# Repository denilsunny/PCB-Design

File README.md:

# PCB-Design
My electronics hardware design and PCB development projects using KiCad.

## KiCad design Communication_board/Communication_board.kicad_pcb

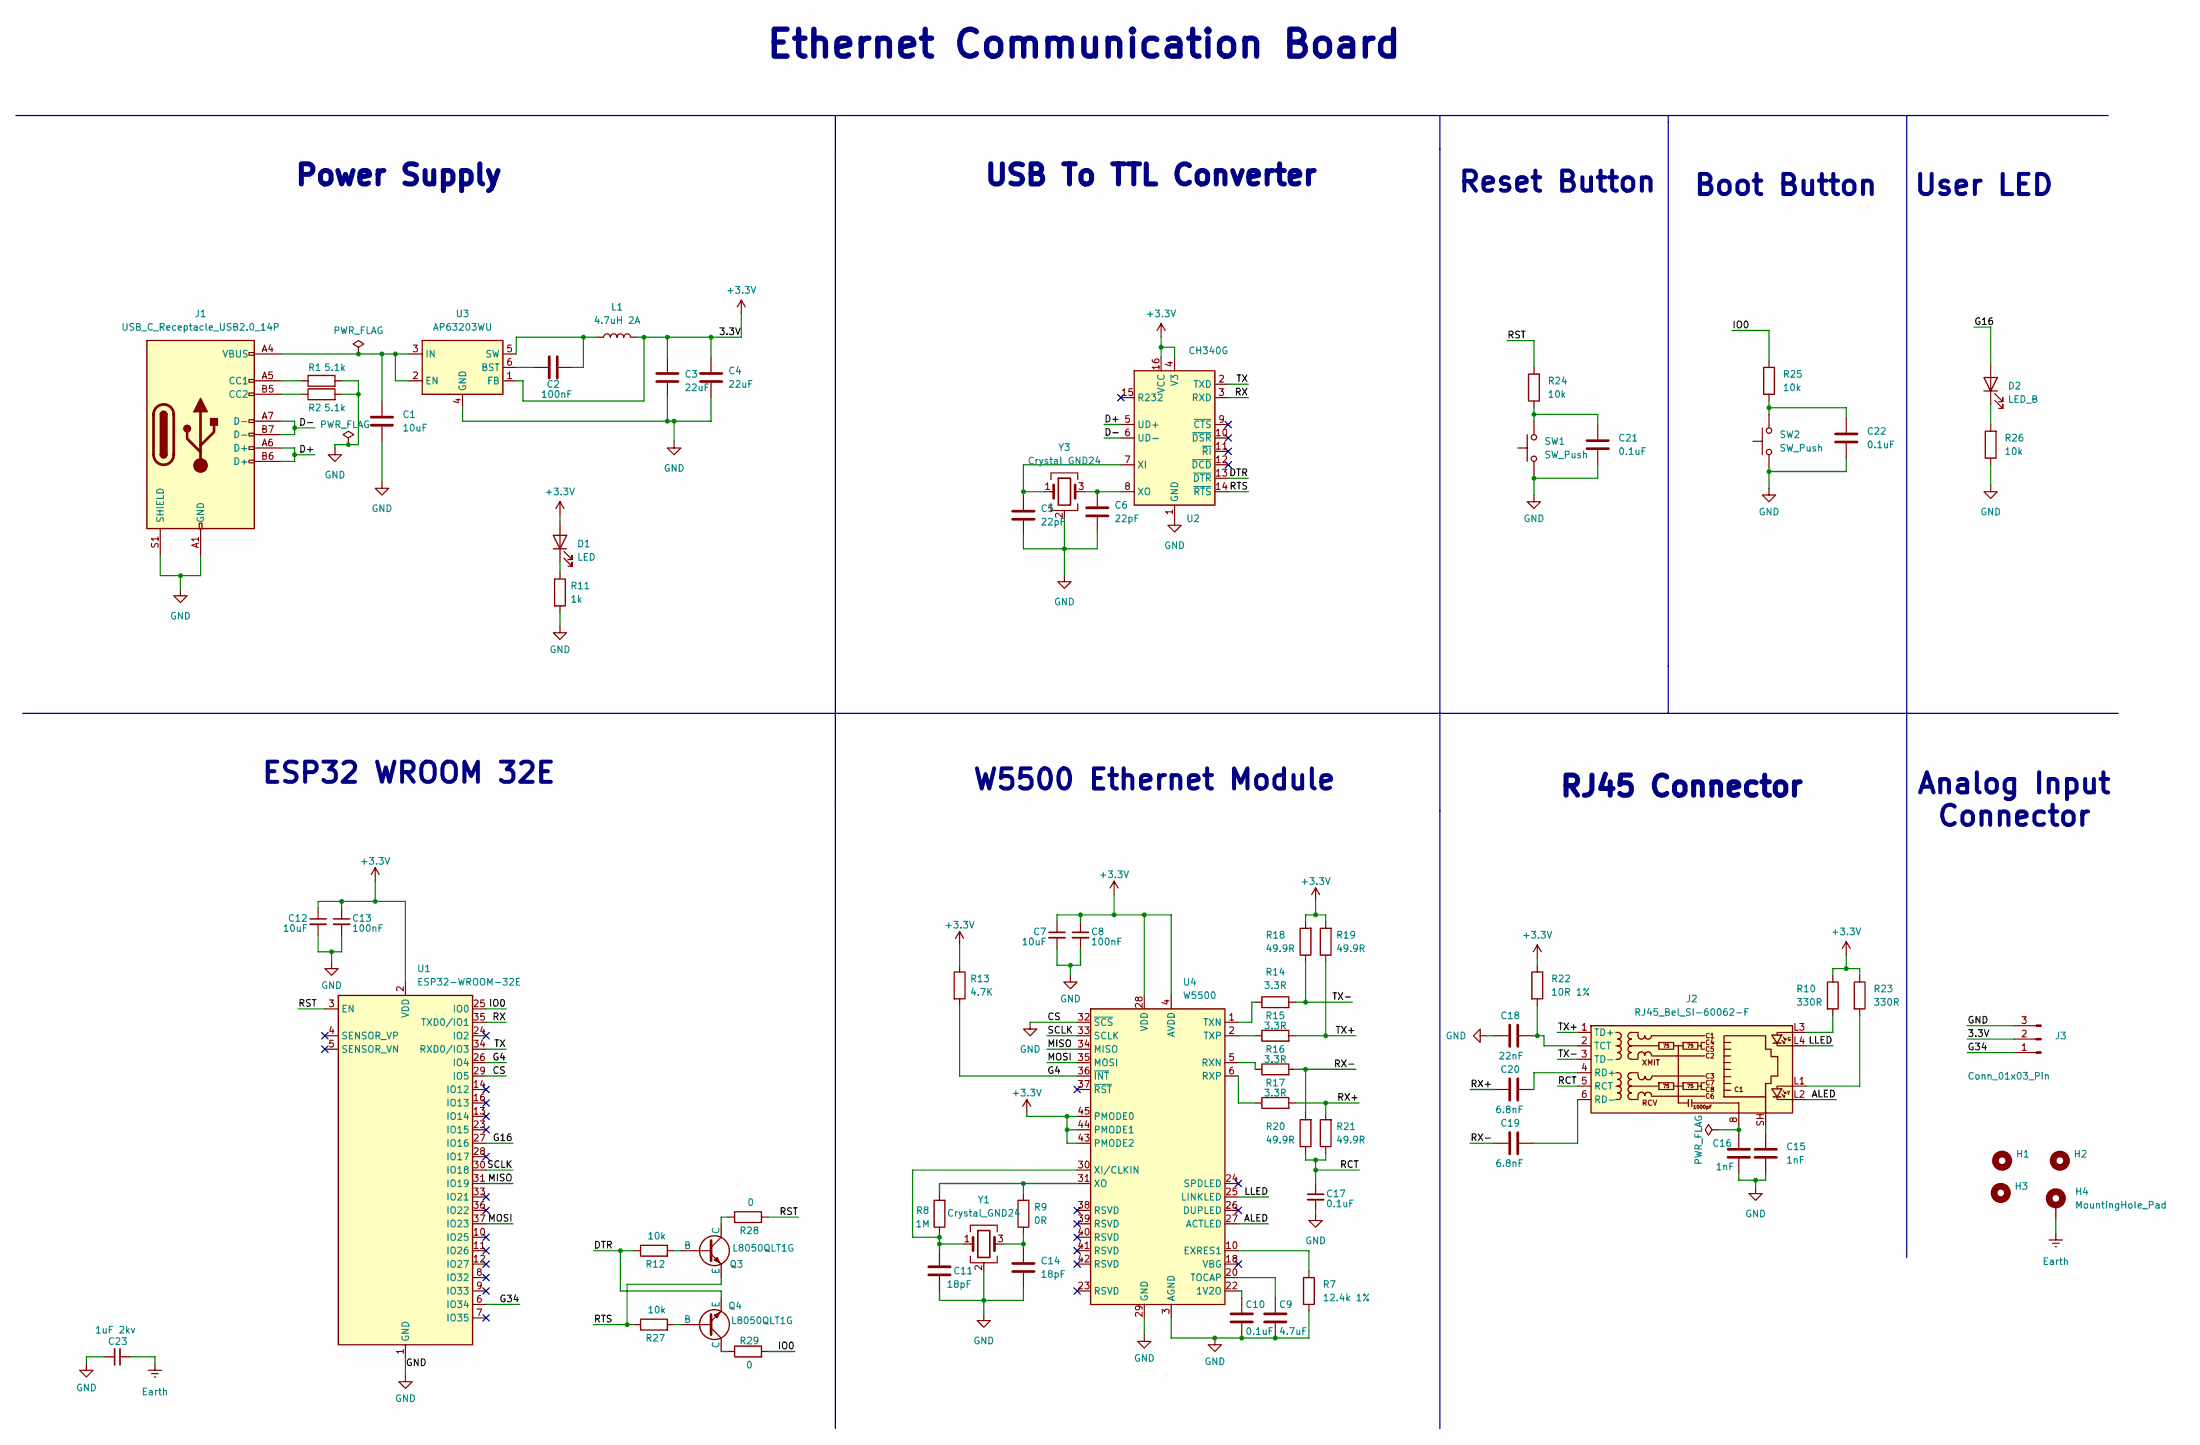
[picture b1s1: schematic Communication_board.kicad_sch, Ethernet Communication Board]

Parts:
C1, C7, C12: 10uF; C_0603_1608Metric
C2, C8, C13: 100nF; C_0603_1608Metric
C3, C4: 22uF; C_0603_1608Metric
C5, C6: 22pF; C_0603_1608Metric
C9: 4.7uF; C_0603_1608Metric
C10, C17, C21, C22: 0.1uF; C_0603_1608Metric
C11, C14: 18pF; C_0603_1608Metric
C15, C16: 1nF; C_0603_1608Metric
C18: 22nF; C_0603_1608Metric
C19, C20: 6.8nF; C_0603_1608Metric
C23: 1uF 2kv; C_0603_1608Metric
D1: LED; LED_0603_1608Metric
D2: LED_B; LED_0603_1608Metric
H1, H2, H3: MountingHole; MountingHole_2.7mm_M2.5
H4: MountingHole_Pad; MountingHole_2.5mm_Pad
J1: USB_C_Receptacle_USB2.0_14P; USB_C_Receptacle_GCT_USB4105-xx-A_16P_TopMnt_Horizontal
J2: RJ45_Bel_SI-60062-F
J3: Conn_01x03_Pin; PinHeader_1x03_P2.54mm_Vertical
L1: 4.7uH 2A; L_Changjiang_FNR252012S
Q3, Q4: L8050QLT1G; SOT-23
R1, R2: 5.1k; R_0603_1608Metric
R7: 12.4k 1%; R_0603_1608Metric
R8: 1M; R_0603_1608Metric
R9: 0R; R_0603_1608Metric
R10, R23: 330R; R_0603_1608Metric
R11: 1k; R_0603_1608Metric
R12, R24, R25, R26, R27: 10k; R_0603_1608Metric
R13: 4.7K; R_0603_1608Metric
R14, R15, R16, R17: 3.3R; R_0603_1608Metric
R18, R19, R20, R21: 49.9R; R_0603_1608Metric
R22: 10R 1%; R_0603_1608Metric
R28, R29: 0; R_0603_1608Metric
SW1, SW2: SW_Push; SW_SPST_PTS810
U1: ESP32-WROOM-32E
U2: CH340G; SOIC-16_3.9x9.9mm_P1.27mm
U3: AP63203WU; TSOT-23-6
U4: W5500; LQFP-48_7x7mm_P0.5mm
Y1, Y3: Crystal_GND24; Crystal_SMD_3225-4Pin_3.2x2.5mm

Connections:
+3.3V: C3.2, C4.2, C7.1, C8.1, C12.1, C13.1, D1.2 (A), J3.2, L1.2, R10.1, R13.1, R18.2, R19.2, R22.1, R23.1, U1.2 (VDD), U2.4 (V3), U2.16 (VCC), U3.1 (FB), U4.4 (AVDD), U4.8 (AVDD), U4.11 (AVDD), U4.15 (AVDD), U4.17 (AVDD), U4.21 (AVDD), U4.28 (VDD), U4.43 (PMODE2), U4.44 (PMODE1), U4.45 (PMODE0)
/ALED: J2.L2, U4.27 (ACTLED)
/D+: J1.A6 (D+), J1.B6 (D+), U2.5 (UD+)
/D-: J1.A7 (D-), J1.B7 (D-), U2.6 (UD-)
/DTR: Q4.3 (E), R12.1, U2.13 (~DTR)
/G4: R13.2, U1.26 (IO4), U4.36 (~INT)
/G16: D2.2 (A), U1.27 (IO16)
/G34: J3.1, U1.6 (IO34)
/IO0: R25.2, R29.2, U1.25 (IO0)
/LLED: J2.L4, U4.25 (LINKLED)
/MISO: U1.31 (IO19), U4.34 (MISO)
/MOSI: U1.37 (IO23), U4.35 (MOSI)
/RCT: C17.1, J2.5 (RCT), R20.1, R21.1
/RST: R24.2, R28.2, U1.3 (EN)
/RTS: Q3.3 (E), R27.1, U2.14 (~RTS)
/RX: U1.35 (TXD0/IO1), U2.3 (RXD)
/RX+: C20.1, R17.2, R21.2
/RX-: C19.1, R16.2, R20.2
/SCLK: U1.30 (IO18), U4.33 (SCLK)
/TX: U1.34 (RXD0/IO3), U2.2 (TXD)
/TX+: J2.1 (TD+), R15.2, R19.1
/TX-: J2.3 (TD-), R14.2, R18.1
Earth: C23.2, H4.1
GND: C1.2, C3.1, C4.1, C5.2, C6.2, C7.2, C8.2, C9.2, C10.2, C11.2, C12.2, C13.2, C14.2, C15.2, C16.2, C17.2, C18.1, C21.2, C22.2, C23.1, J1.A1 (GND), J1.A12 (GND), J1.B1 (GND), J1.B12 (GND), J1.S1 (SHIELD), J3.3, R1.2, R2.2, R7.2, R11.2, R26.1, SW1.1, SW2.1, U1.1 (GND), U1.15 (GND), U1.29 (IO5), U1.38 (GND), U1.39 (GND), U2.1 (GND), U3.4 (GND), U4.3 (AGND), U4.9 (AGND), U4.14 (AGND), U4.16 (AGND), U4.19 (AGND), U4.29 (GND), U4.32 (~SCS), U4.48 (AGND), Y1.2 (G), Y1.4 (G), Y3.2 (G), Y3.4 (G)
unnamed: C14.1, R9.1, Y1.3
unnamed: C15.1, J2.SH
unnamed: C16.1, J2.8
unnamed: C21.1, R24.1, SW1.2
unnamed: C22.1, R25.1, SW2.2
unnamed: D1.1 (K), R11.1
unnamed: D2.1 (K), R26.2
unnamed: J1.A5 (CC1), R1.1
unnamed: J1.B5 (CC2), R2.1
unnamed: J2.L1, R23.2
unnamed: J2.L3, R10.2
unnamed: C20.2, J2.4 (RD+)
unnamed: C19.2, J2.6 (RD-)
unnamed: C18.2, J2.2 (TCT), R22.2
unnamed: Q3.2 (B), R12.2
unnamed: Q3.1 (C), R28.1
unnamed: Q4.2 (B), R27.2
unnamed: Q4.1 (C), R29.1
unnamed: C5.1, U2.7 (XI), Y3.1
unnamed: C6.1, U2.8 (XO), Y3.3
unnamed: C2.1, U3.6 (BST)
unnamed: C1.1, J1.A4 (VBUS), J1.A9 (VBUS), J1.B4 (VBUS), J1.B9 (VBUS), U3.2 (EN), U3.3 (IN)
unnamed: C2.2, L1.1, U3.5 (SW)
unnamed: C10.1, U4.22 (1V2O)
unnamed: R7.1, U4.10 (EXRES1)
unnamed: R16.1, U4.5 (RXN)
unnamed: R17.1, U4.6 (RXP)
unnamed: C9.1, U4.20 (TOCAP)
unnamed: R14.1, U4.1 (TXN)
unnamed: R15.1, U4.2 (TXP)
unnamed: C11.1, R8.1, U4.30 (XI/CLKIN), Y1.1
unnamed: R8.2, R9.2, U4.31 (XO)

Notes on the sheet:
ESP32 WROOM 32E
Power Supply
Boot Button
Analog Input Connector
USB To TTL Converter
Reset Button
Ethernet Communication Board
User LED
W5500 Ethernet Module
RJ45 Connector

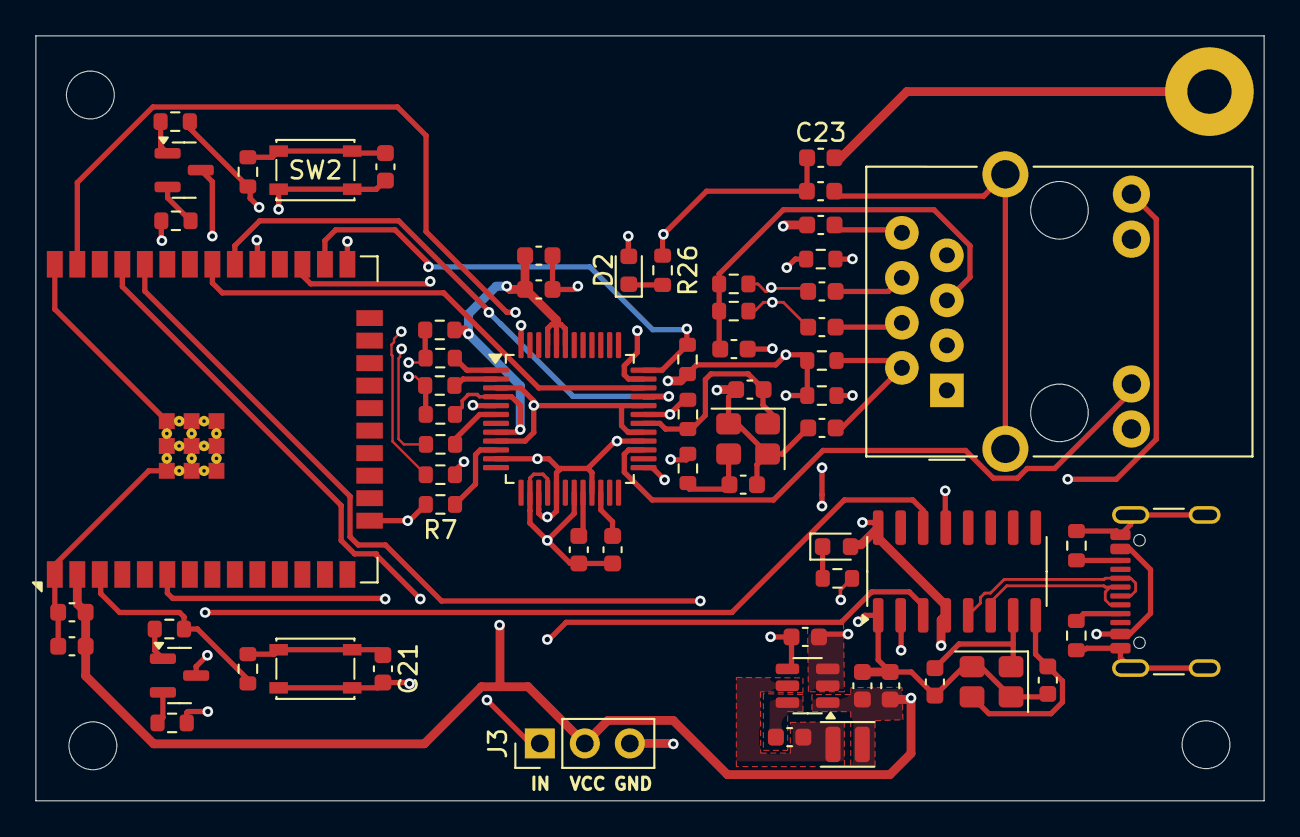
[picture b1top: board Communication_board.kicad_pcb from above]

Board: 4 copper layers, 69.3 x 43.2 mm, 68 parts (0 on the bottom side), 56 nets.

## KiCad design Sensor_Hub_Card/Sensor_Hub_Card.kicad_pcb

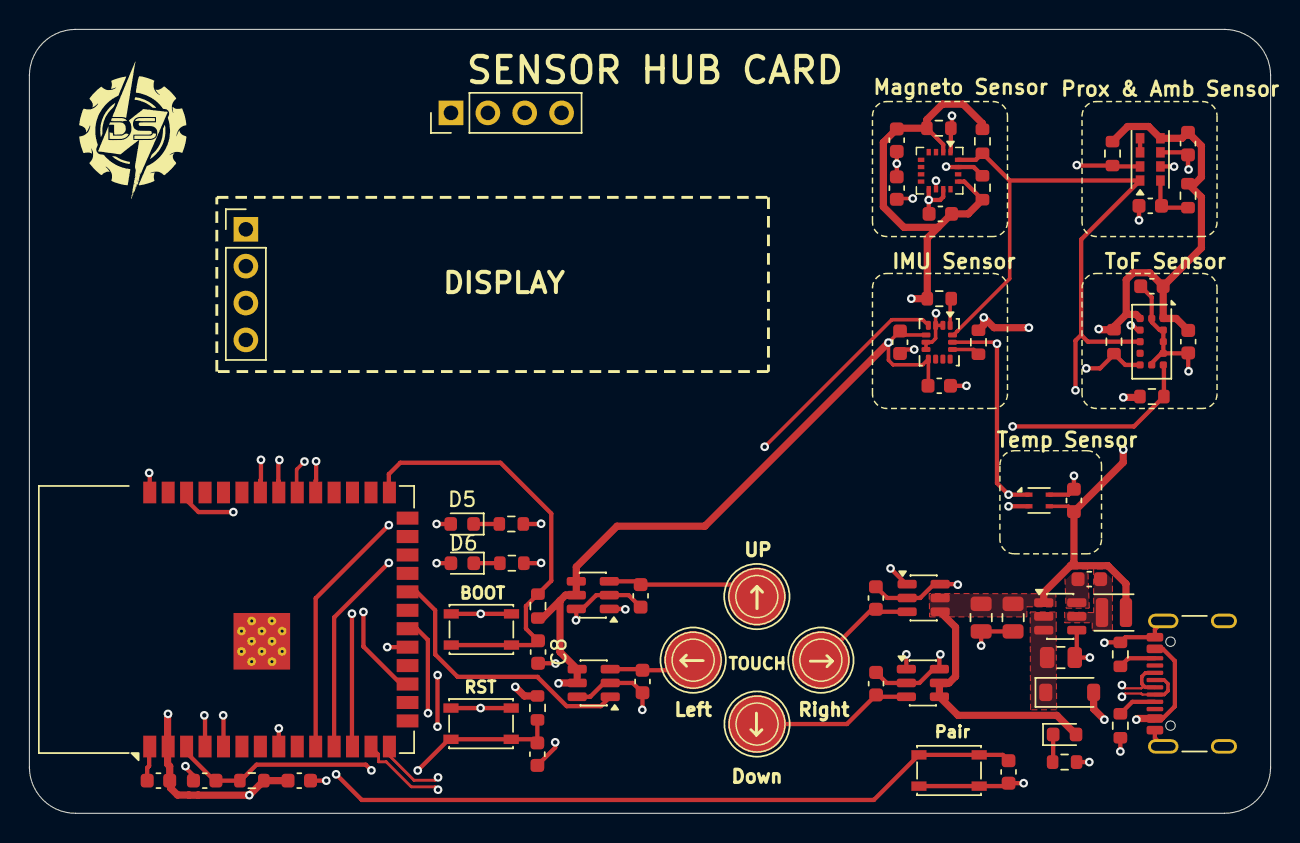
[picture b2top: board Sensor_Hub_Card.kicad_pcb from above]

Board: 4 copper layers, 85.5 x 54.0 mm, 67 parts (0 on the bottom side), 40 nets.

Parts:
C1, C17: 10uF; C_0603_1608Metric
C2, C4, C9, C10, C11, C14: 100nF; C_0603_1608Metric
C3: 10uF; C_0805_2012Metric
C5, C7: 22uF; C_0805_2012Metric
C8, C20: 0.1uF; C_0603_1608Metric
C12, C13, C16, C18, C19, C22: 1uF; C_0603_1608Metric
C15: 4.7nF; C_0603_1608Metric
C23, C26, C27, C28: 30pF; C_0603_1608Metric
D1: B5819W; D_SOD-123
D2, D5, D6: LED_R; LED_0603_1608Metric
Down: Touch; TestPoint_Pad_D4.0mm
J1: USB4500-03-0-A; USB_C_Receptacle_GCT_USB4105-xx-A_16P_TopMnt_Horizontal
J2, J2#2: Conn_01x04; PinHeader_1x04_P2.54mm_Vertical
L1: 4.7uH 2A; L_Changjiang_FNR252012S
Left: Touch; TestPoint_Pad_D4.0mm
R1, R16: 10K; R_0603_1608Metric
R2, R3: 5.1k; R_0603_1608Metric
R4, R5, R6: 1K; R_0603_1608Metric
R7, R8, R9, R11, R12, R13, R14, R15, R17: 10k; R_0603_1608Metric
R10: 22; R_0603_1608Metric
Right: Touch; TestPoint_Pad_D4.0mm
SW2, SW2#2, SW4: SW_Push; SW_SPST_PTS810
TP6: Touch; TestPoint_Pad_D4.0mm
U1: ESP32-S3-WROOM-1
U2: AP63203WU; TSOT-23-6
U3: SHT4x; Sensirion_DFN-4_1.5x1.5mm_P0.8mm_SHT4x_NoCentralPad
U4: LSM6DS3; LGA-14_3x2.5mm_P0.5mm_LayoutBorder3x4y
U5: APDS-9960; Avago_APDS-9960
U6: VL53L1CXV0FY1; ST_VL53L1x
U7: MMC5883MA; LGA-16_3x3mm_P0.5mm
U10, U13, U14, U15: TTP223-BA6; SOT-23-6

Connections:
+3.3V: C1.1, C2.1, C5.1, C7.1, C9.1, C10.1, C11.1, C13.2, C14.1, C15.1, C16.2, C18.2, D2.2 (A), J2.1, J2#2.1, L1.2, R1.1, R7.2, R8.2, R9.2, R10.2, R11.2, R12.2, R13.2, R14.2, R15.2, R16.1, R17.1, U1.2 (3V3), U2.1 (FB), U3.3 (VDD), U4.5 (VDDIO), U4.8 (VDD), U5.5 (LED_A), U6.1 (AVDDVCSEL), U6.11 (AVDD), U7.2 (VDD), U7.13 (VDDIO), U10.4 (AHLB), U10.5 (VDD), U13.4 (AHLB), U13.5 (VDD), U14.4 (AHLB), U14.5 (VDD), U15.4 (AHLB), U15.5 (VDD)
/Boot: C8.1, R17.2, SW2.2, U1.27 (IO0)
/D+: J1.A6 (D+), J1.B6 (D+), U1.14 (USB_D+)
/D-: J1.A7 (D-), J1.B7 (D-), U1.13 (USB_D-)
/GPIO1: R13.1, U1.31 (IO38), U6.7 (GPIO1)
/INT1: U1.32 (IO39), U4.4 (INT1)
/INTAD: R9.1, U1.33 (IO40), U5.2 (INT)
/INTMG: R15.1, U1.34 (IO41), U7.15 (INT)
/LED1: D5.2 (A), U1.10 (IO17)
/LED2: D6.2 (A), U1.11 (IO18)
/Pair: C22.1, SW4.2, U1.8 (IO15)
/RST: C19.1, C20.1, R1.2, R16.2, SW2#2.2, U1.3 (EN)
/SCL: R14.1, U1.17 (IO9), U3.1 (SDA), U4.13 (SCL), U5.7 (SCL), U6.10 (SCL), U7.1 (SCL)
/SCL1: J2.4, J2#2.4, U1.5 (IO5)
/SDA: R11.1, U1.12 (IO8), U3.2 (SCL), U4.14 (SDA), U5.1 (SDA), U6.9 (SDA), U7.16 (SDA)
/SDA1: J2.3, J2#2.3, U1.4 (IO4)
/T1: U1.19 (IO11), U10.1 (Q)
/T2: U1.20 (IO12), U14.1 (Q)
/T3: U1.21 (IO13), U13.1 (Q)
/T4: U1.22 (IO14), U15.1 (Q)
/XSHUNT: R12.1, U1.38 (IO2), U6.5 (XSHUT)
GND: C1.2, C2.2, C3.2, C5.2, C7.2, C8.2, C9.2, C10.2, C11.2, C12.2, C13.1, C14.2, C15.2, C16.1, C17.1, C18.1, C19.2, C20.2, C22.2, C23.2, C26.2, C27.2, C28.2, J1.A1 (GND), J1.A12 (GND), J1.B1 (GND), J1.B12 (GND), J1.S1 (SHIELD), J2.2, J2#2.2, R2.2, R3.2, R4.2, R5.2, R6.2, SW2.1, SW2#2.1, SW4.1, U1.1 (GND), U1.40 (GND), U1.41 (GND), U2.4 (GND), U3.4 (VSS), U4.2 (SDX), U4.3 (SCX), U4.6 (GND), U4.7 (GND), U5.6 (GND), U6.2 (AVSSVCSEL), U6.3 (GND), U6.4 (GND), U6.6 (GND), U6.12 (GND), U7.9 (GND), U7.11 (GND), U10.2 (VSS), U10.6 (TOG), U13.2 (VSS), U13.6 (TOG), U14.2 (VSS), U14.6 (TOG), U15.2 (VSS), U15.6 (TOG)
unnamed: C3.1, D1.1 (K), U2.2 (EN), U2.3 (IN)
unnamed: D2.1 (K), R5.1
unnamed: D5.1 (K), R4.1
unnamed: D6.1 (K), R6.1
unnamed: J1.A5 (CC1), R2.1
unnamed: J1.B5 (CC2), R3.1
unnamed: C4.2, U2.6 (BST)
unnamed: C4.1, L1.1, U2.5 (SW)
unnamed: R7.1, U4.12 (CS)
unnamed: R8.1, U4.1 (SDO/SA0)
unnamed: U5.3 (LDR), U5.4 (LED_K)
unnamed: C12.1, R10.1, U5.8 (VDD)
unnamed: C17.2, U7.10 (CAP)
unnamed: C23.1, Right.1, U10.3 (I)
unnamed: C26.1, TP6.1, U13.3 (I)
unnamed: C27.1, Down.1, U14.3 (I)
unnamed: C28.1, Left.1, U15.3 (I)
VBUS: D1.2 (A), J1.A4 (VBUS), J1.A9 (VBUS), J1.B4 (VBUS), J1.B9 (VBUS)

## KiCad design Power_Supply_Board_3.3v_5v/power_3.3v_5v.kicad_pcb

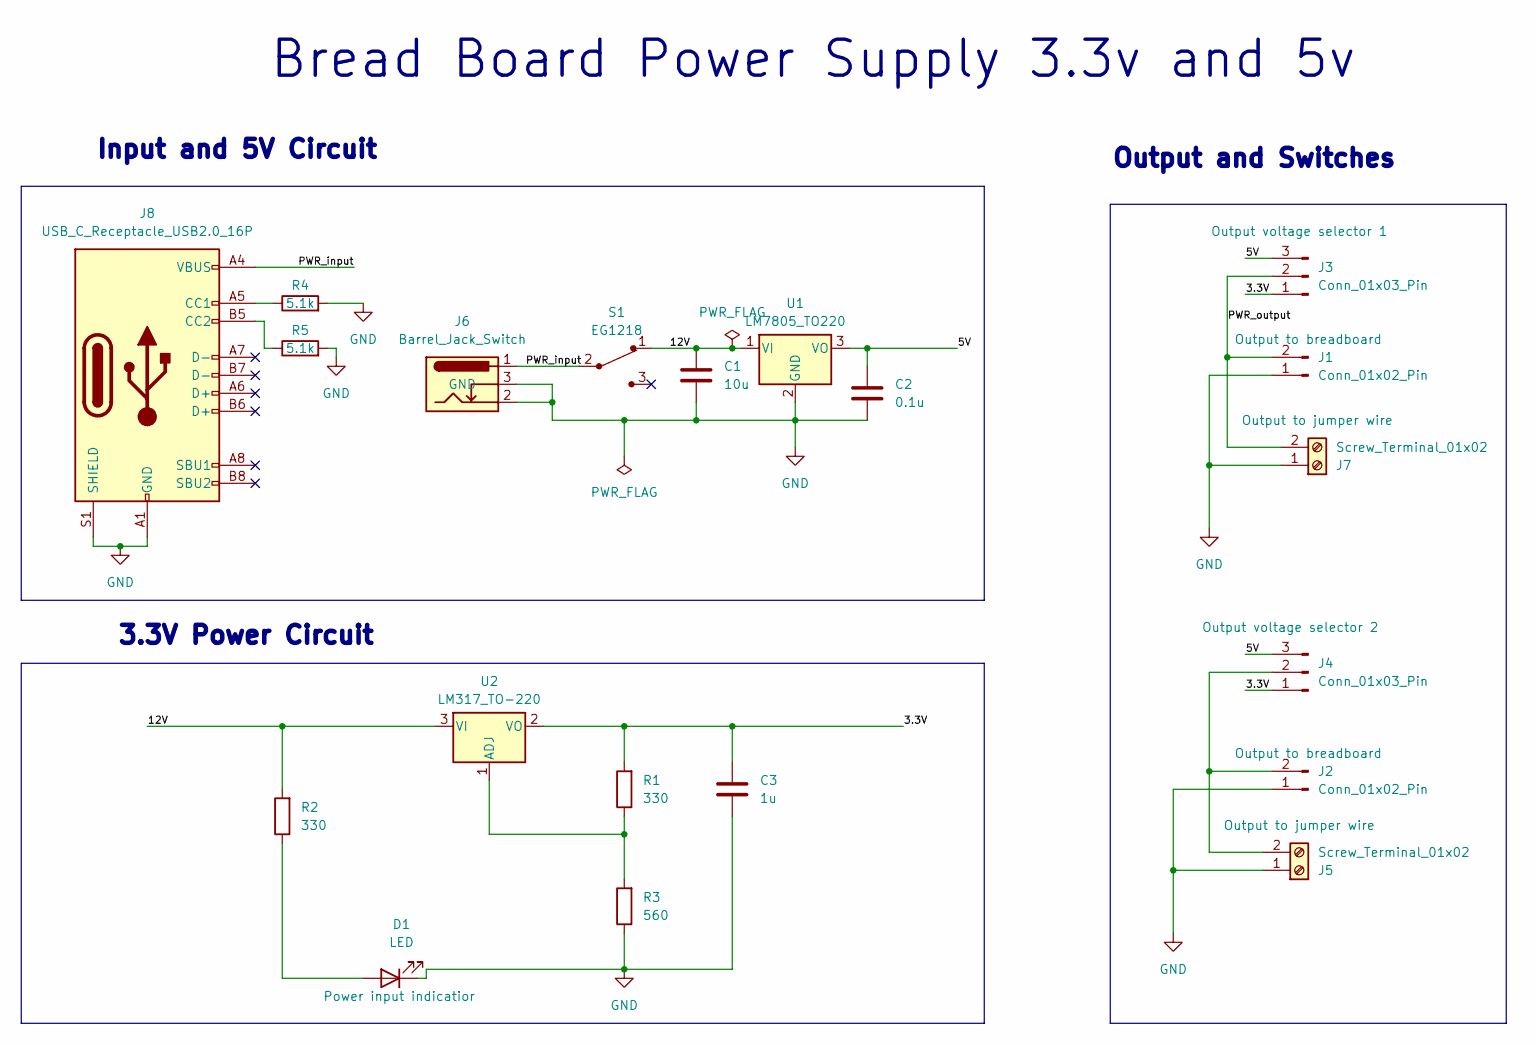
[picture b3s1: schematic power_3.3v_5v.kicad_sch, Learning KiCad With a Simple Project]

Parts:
C1: 10u; C_Disc_D3.0mm_W1.6mm_P2.50mm
C2: 0.1u; C_Disc_D3.0mm_W1.6mm_P2.50mm
C3: 1u; C_Disc_D3.0mm_W1.6mm_P2.50mm
D1: LED; LED_D5.0mm
J1, J2: Conn_01x02_Pin; PinHeader_1x02_P2.54mm_Vertical
J3, J4: Conn_01x03_Pin; PinHeader_1x03_P2.54mm_Vertical
J5, J7: Screw_Terminal_01x02; TerminalBlock_bornier-2_P5.08mm
J6: Barrel_Jack_Switch; BarrelJack_Horizontal
J8: USB_C_Receptacle_USB2.0_16P; USB_C_Receptacle_HCTL_HC-TYPE-C-16P-01A
R1, R2: 330; R_Axial_DIN0204_L3.6mm_D1.6mm_P7.62mm_Horizontal
R3: 560; R_Axial_DIN0204_L3.6mm_D1.6mm_P7.62mm_Horizontal
R4, R5: 5.1k; R_Axial_DIN0204_L3.6mm_D1.6mm_P7.62mm_Horizontal
S1: EG1218; Switch_Slide_11.6x4mm_EG1218; MPN EG1218; Digi-Key_PN EG1903-ND
U1: LM7805_TO220; TO-220-3_Vertical
U2: LM317_TO-220; TO-220-3_Vertical

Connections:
/3.3V: C3.1, J3.1, J4.1, R1.2, U2.2 (VO)
/5V: C2.1, J3.3, J4.3, U1.3 (VO)
/12V: C1.1, R2.2, S1.1, U1.1 (VI), U2.3 (VI)
/PWR_input: J6.1, J8.A4 (VBUS), J8.A9 (VBUS), J8.B4 (VBUS), J8.B9 (VBUS), S1.2
/PWR_output: J1.2, J3.2, J7.2
GND: C1.2, C2.2, C3.2, D1.1 (K), J1.1, J2.1, J5.1, J6.2, J6.3, J7.1, J8.A1 (GND), J8.A12 (GND), J8.B1 (GND), J8.B12 (GND), J8.S1 (SHIELD), R3.1, R4.2, R5.2, U1.2 (GND)
unnamed: D1.2 (A), R2.1
unnamed: J2.2, J4.2, J5.2
unnamed: J8.A5 (CC1), R4.1
unnamed: J8.B5 (CC2), R5.1
unnamed: R1.1, R3.2, U2.1 (ADJ)

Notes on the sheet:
Input and 5V Circuit
3.3V Power Circuit
Output and Switches
Bread Board Power Supply 3.3v and 5v

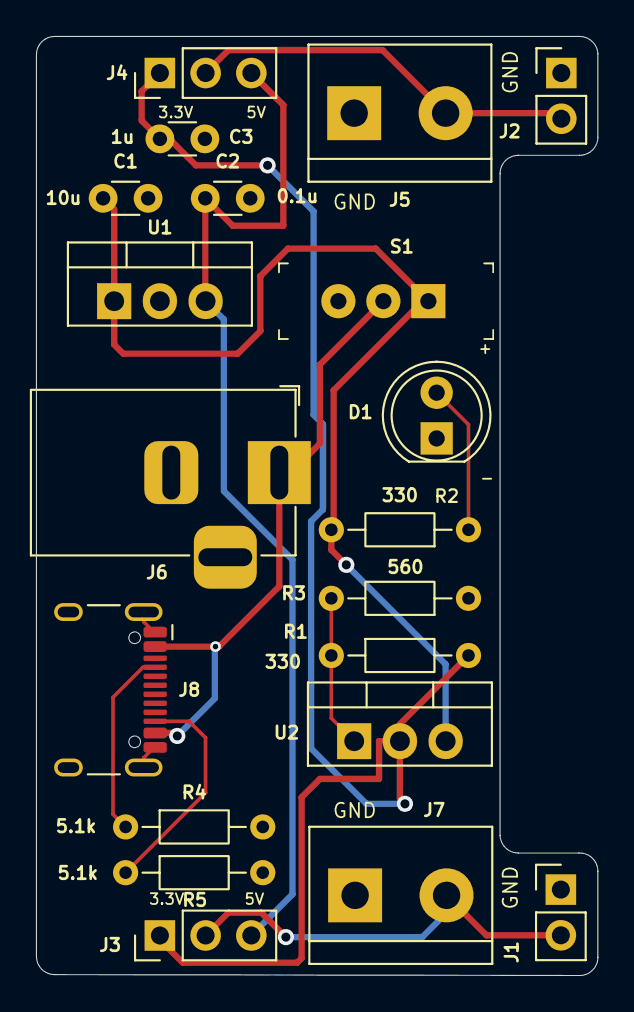
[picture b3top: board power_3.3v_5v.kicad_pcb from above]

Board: 2 copper layers, 31.2 x 52.2 mm, 20 parts (0 on the bottom side), 11 nets.
